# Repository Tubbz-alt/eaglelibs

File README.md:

# eaglelibs
Electronic Component  Libraries on EAGLE
It is some Eagle libraries and circuits that I used on my project.

It include,
  TI-HDC1080(Humidity Sensor with temperature sensor)(http://www.ti.com/product/HDC1080)
  TI-CC2650MODA(Bluetooth, low energy Wireless MCU Module)(http://www.ti.com/product/CC2650MODA )
  TI-LP5907(Regulator)(http://www.ti.com/product/LP5907)
  LIR2450 3.6V Battery (https://www.digikey.com/product-detail/en/sparkfun-electronics/PRT-10319/PRT-10319-ND/5271300)
  Datasheets of the components.

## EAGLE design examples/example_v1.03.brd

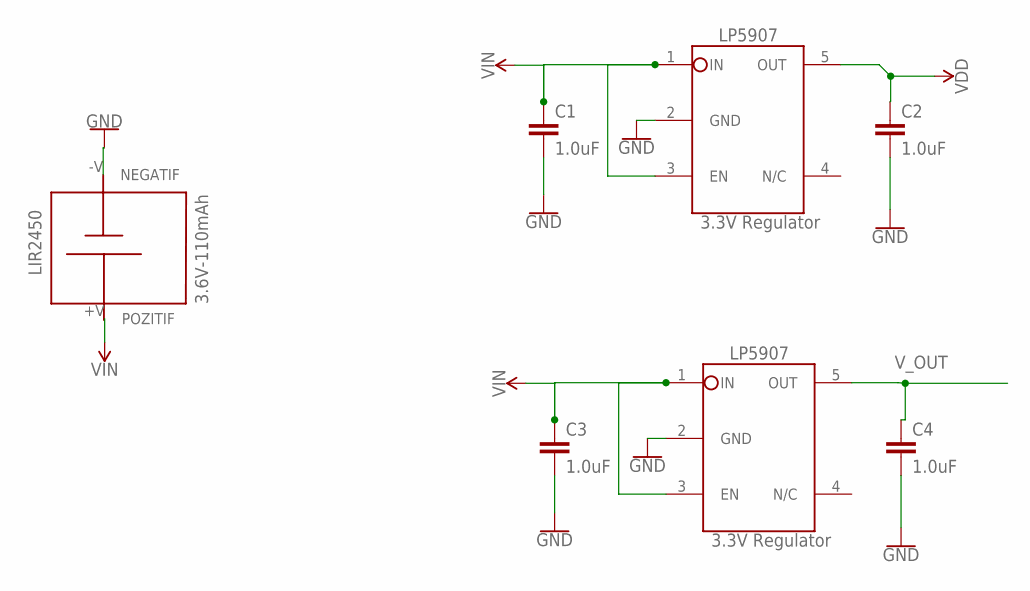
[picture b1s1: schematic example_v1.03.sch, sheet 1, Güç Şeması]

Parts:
C1, C2, C3, C4: 1.0uF; 1206
CC2650MODA: 3.3V Regulator; SOT-23
HDC1080: 3.3V Regulator; SOT-23
U$1: LIR2450; BATTERYHOLDER

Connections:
GND: C1.2, C2.2, C3.2, C4.2, CC2650MODA.2 (GND), HDC1080.2 (GND), U$1.-V (NEGATIF); also elsewhere on the board
VDD: C2.1, HDC1080.5 (OUT); also elsewhere on the board
VIN: C1.1, C3.1, CC2650MODA.1 (IN), CC2650MODA.3 (EN), HDC1080.1 (IN), HDC1080.3 (EN), U$1.+V (POZITIF)
V_OUT: C4.1, CC2650MODA.5 (OUT); also elsewhere on the board

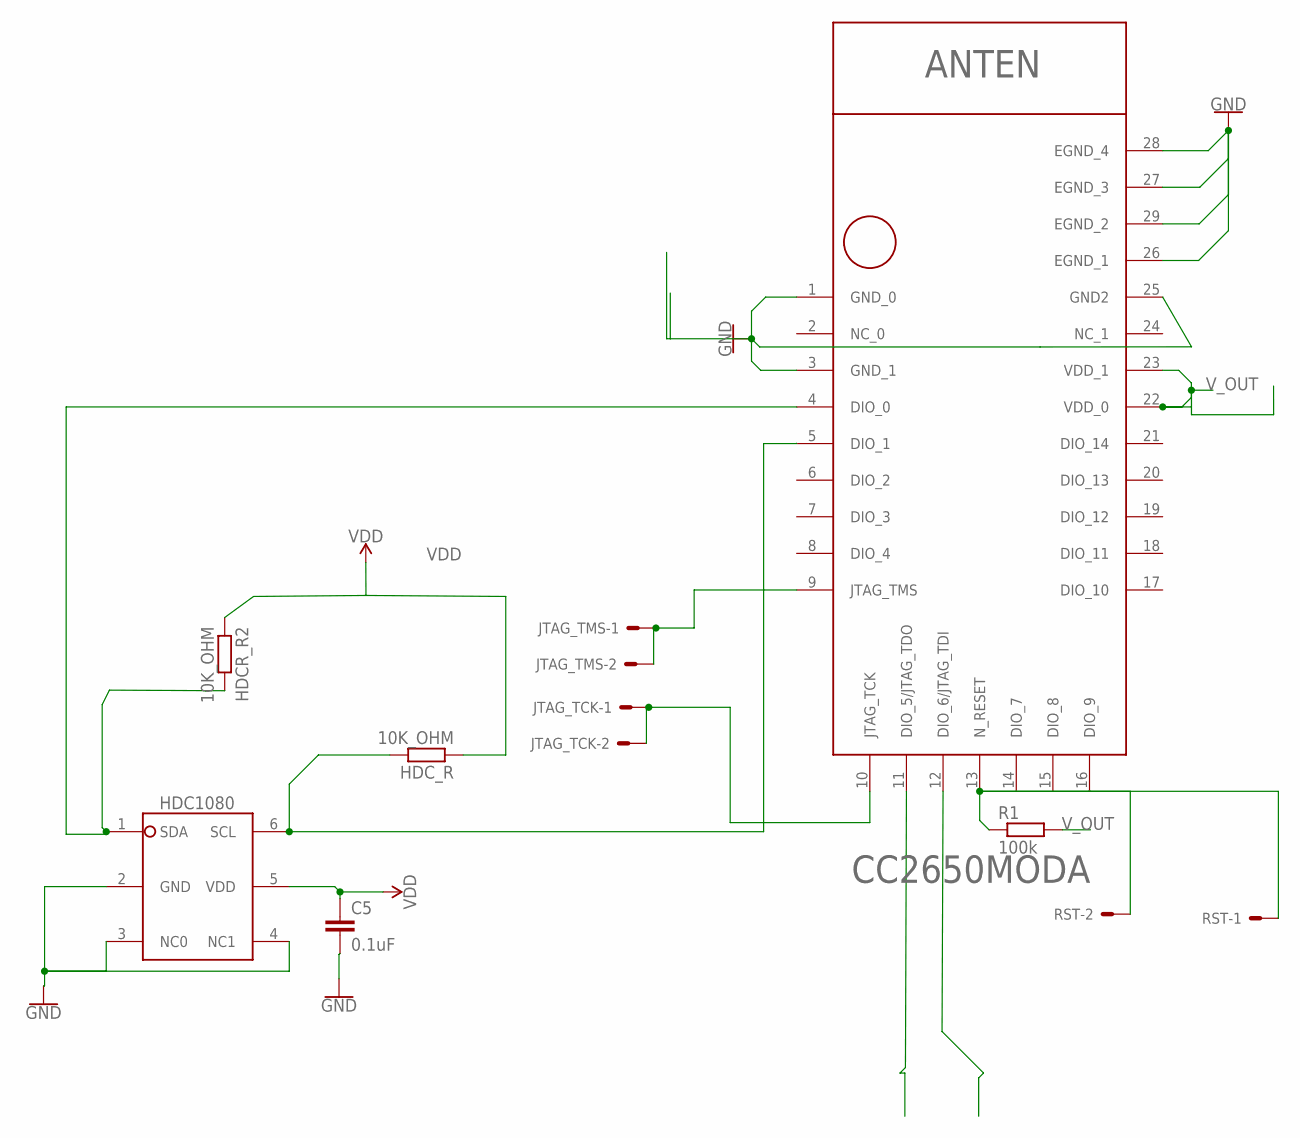
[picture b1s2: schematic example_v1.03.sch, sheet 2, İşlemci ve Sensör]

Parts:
C5: 0.1uF; 0603
HDCR_R2: 10K_OHM; R2012
HDC_R: 10K_OHM; R2012
JTAG_TCK: 332-02
JTAG_TMS: 332-02
R1: 100k; R2012
RST: 332-02
U$2: HDC1080; WSONDMB006A
U$3: CC2650MODA; MOH0029A-QFM

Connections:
GND: C5.2, U$2.2 (GND), U$2.3 (NC0), U$2.4 (NC1), U$3.1 (GND_0), U$3.3 (GND_1), U$3.25 (GND2), U$3.26 (EGND_1), U$3.27 (EGND_3), U$3.28 (EGND_4), U$3.29 (EGND_2); also elsewhere on the board
unnamed: JTAG_TMS.1, JTAG_TMS.2, U$3.9 (JTAG_TMS)
unnamed: JTAG_TCK.1, JTAG_TCK.2, U$3.10 (JTAG_TCK)
unnamed: R1.1, RST.1, RST.2, U$3.13 (N_RESET)
unnamed: HDCR_R2.2, U$2.1 (SDA), U$3.4 (DIO_0)
unnamed: HDC_R.2, U$2.6 (SCL), U$3.5 (DIO_1)
VDD: C5.1, HDCR_R2.1, HDC_R.1, U$2.5 (VDD); also elsewhere on the board
V_OUT: R1.2, U$3.22 (VDD_0), U$3.23 (VDD_1); also elsewhere on the board

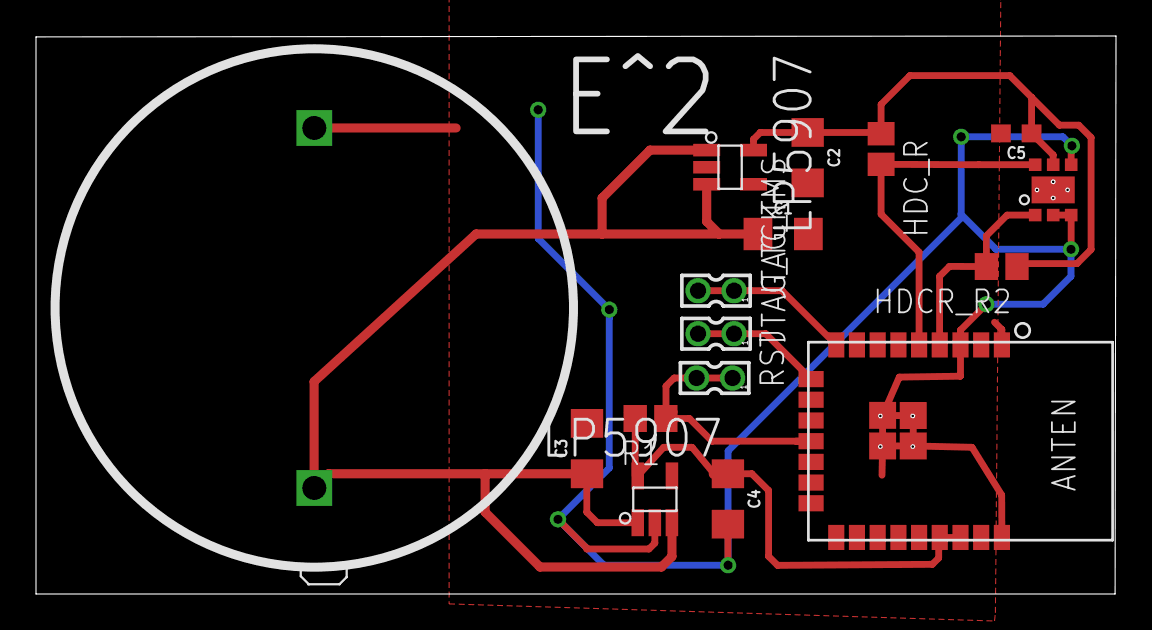
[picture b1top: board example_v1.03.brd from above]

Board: 2 copper layers, 60.0 x 31.0 mm, 16 parts (0 on the bottom side), 9 nets.

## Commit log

2018-02-22 deneme py
2018-02-22 cc2650moda datasheet
2018-02-22 battery
2018-02-22 all files and libraries that I have
2018-02-22 bazı noktaları vurguladm
2018-02-22 isaretlemeler yaptık
2018-02-27 Circuit Board PCB
2018-02-27 Shematic of PCB
2018-03-05 2. example of the circuit-sch
2018-03-05 version updated to 1.03
2018-03-05 Version updated to version 1.05
2018-03-05 version updated to 1.05
2018-03-05 Pictures of sch files
2018-03-08 ne oluyor
2018-03-08 new examples
2018-03-08 Dataheets
2018-07-16 Image of vs1.07

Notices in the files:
parts and their libraries:
SparkFun-Capacitors: Licensing: Creative Commons ShareAlike 4.0 International - https://creativecommons.org/licenses/by-sa/4.0
